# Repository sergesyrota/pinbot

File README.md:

```bash
brew install --HEAD opencv3 --with-contrib
brew install webp

pip install --upgrade pip
pip install virtualenv

echo /usr/local/opt/opencv3/lib/python2.7/site-packages >> /usr/local/lib/python2.7/site-packages/opencv3.pth

# Reload terminal

cd path/to/pinbot

virtualenv -p `which python` .virtualenv
source .virtualenv/bin/activate

pip install -r requirements.txt

```

### Debugging

For debugging place following in the code:

```python
import ipdb; ipdb.set_trace()
```

For debugging serial communication:

```
$ socat -d -d pty,raw,echo=0 pty,raw,echo=0
2016/11/29 08:41:25 socat[43296] N PTY is /dev/ttys003
2016/11/29 08:41:25 socat[43296] N PTY is /dev/ttys004
```
This will create forwarding between 2 serial interfaces. Then you can write into one, and read from another.

Flipper detect frame numbers:

When we want to train flipper on recorded video, we need to know frame numbers that can be considered as "pressing
the button." Both arguments need to be passed (otherwise it doesn't make much sense).

```
--debug-right 244,273,316,349,381,413,445,476,522
--debug-left 594,626,658,691,723,755,787
```

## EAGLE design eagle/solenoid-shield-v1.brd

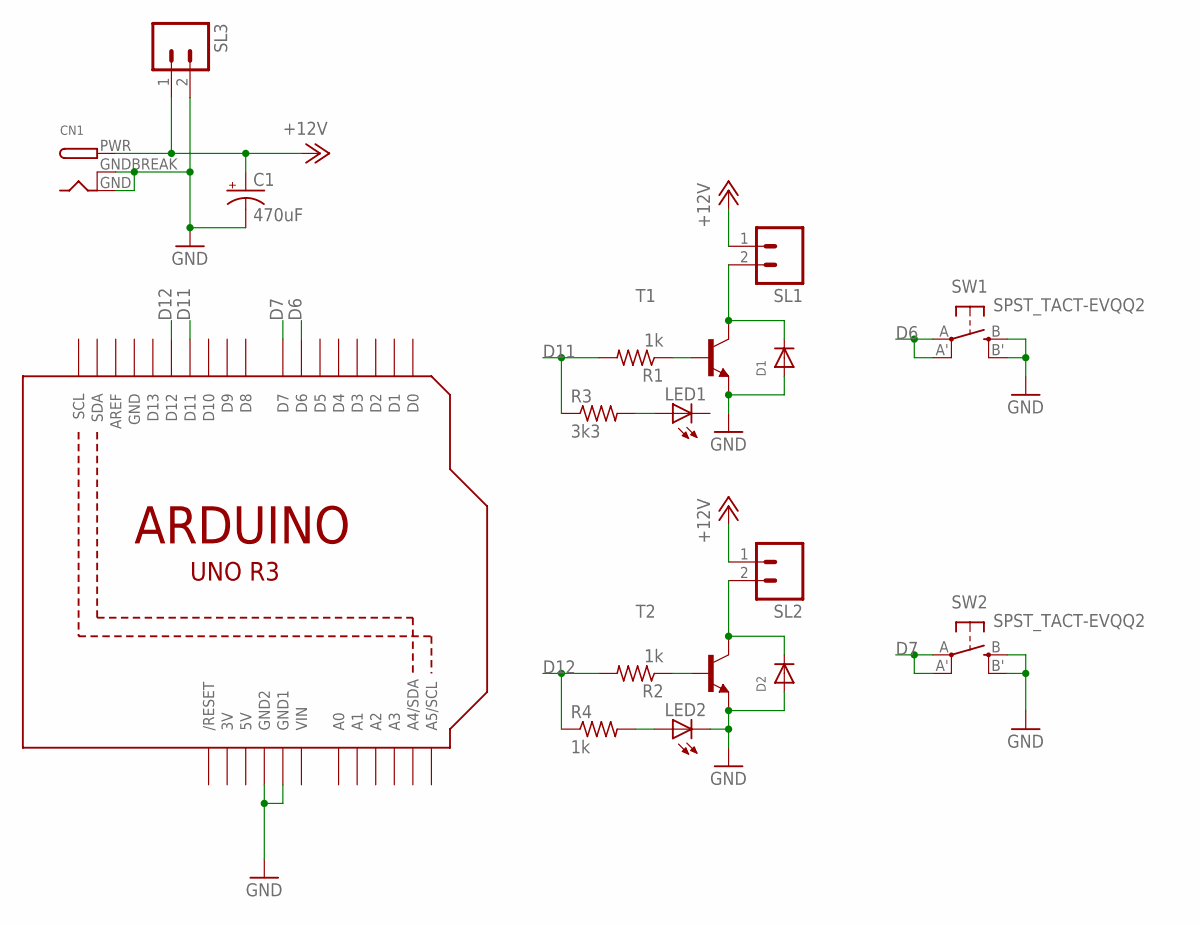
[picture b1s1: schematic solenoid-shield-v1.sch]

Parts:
C1: 470uF; E5-13
CN1: DCBARRELPTH; DCJACK_2MM_PTH
D1, D2: DIODESMA; SMADIODE
LED1, LED2: LEDSMT1206; 1206
Q1: ARDUINOR3-NOIOREF-NOTEXT; ARDUINOR3-NOTEXT-NOIOREF
R1, R2, R4: 1k; R0603
R3: 3k3; R0603
SL1, SL2, SL3: M02; 02P
SW1, SW2: SPST_TACT-EVQQ2; EVQ-Q2
T1, T2: BC808-NPN-SOT23-BEC; SOT23-BEC

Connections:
3V: Q1.3V
5V: Q1.5V
+12V: C1.+, CN1.PWR, SL1.1, SL2.1, SL3.1
D6: Q1.D6, SW1.A, SW1.A' (P1)
D7: Q1.D7, SW2.A, SW2.A' (P1)
D11: Q1.D11, R1.2, R3.1
D12: Q1.D12, R2.2, R4.1
GND: C1.-, CN1.GND, CN1.GNDBREAK, D1.A, D2.A, LED2.C, Q1.GND, Q1.GND1, Q1.GND2, SL3.2, SW1.B (S), SW1.B' (S1), SW2.B (S), SW2.B' (S1), T1.E, T2.E
unnamed: LED2.A, R4.2
unnamed: R1.1, T1.B
unnamed: D1.C, SL1.2, T1.C
unnamed: LED1.A, R3.2
unnamed: D2.C, SL2.2, T2.C
unnamed: R2.1, T2.B
VIN: Q1.VIN

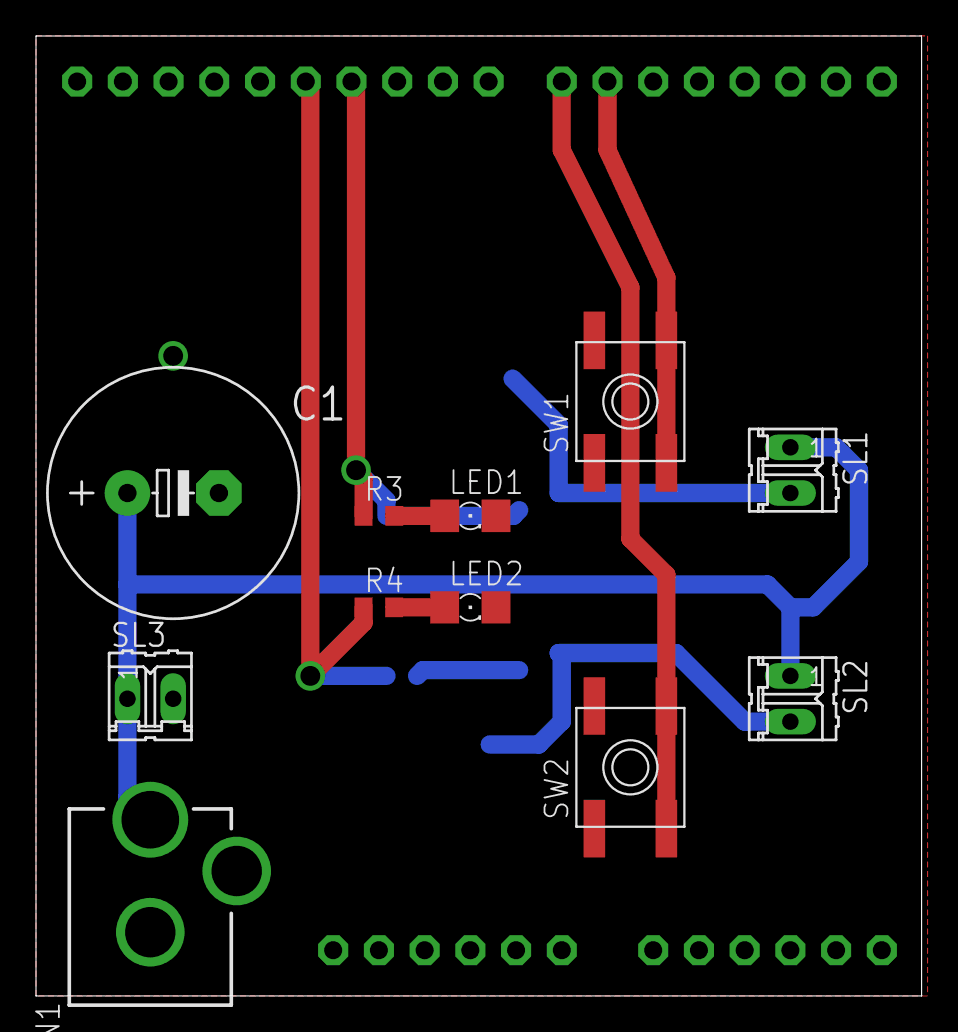
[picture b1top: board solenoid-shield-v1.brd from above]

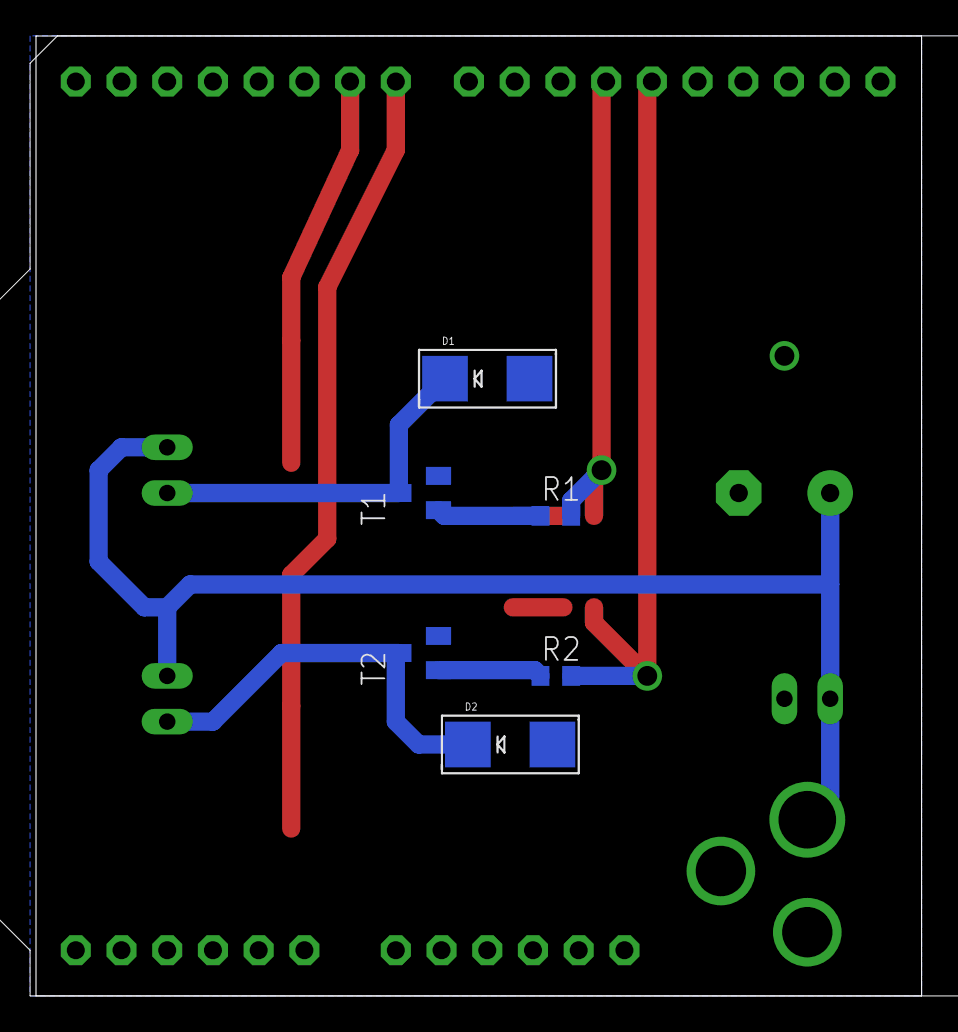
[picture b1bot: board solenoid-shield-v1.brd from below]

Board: 2 copper layers, 49.2 x 53.3 mm, 18 parts (6 on the bottom side), 12 nets.

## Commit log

2016-11-19 Initial prototype of tracker
2016-11-19 Adding gitignore
2016-11-19 Adding basic installation steps
2016-11-19 Fixed readme formatting
2016-11-19 Add tmp and log folders
2016-11-19 Using argparse to specify video source
2016-11-19 Testing multi-ball
2016-11-19 Mention dependencies installation
2016-11-19 Specify OpenCV installation procedure to include all required libraries
2016-11-19 Remove pep8 violations
2016-11-23 Adding 3d model for micro-solenoid model git status
2016-11-23 Removing highlights for some cutouts of the model, so it looks clearer.
2016-11-23 adding some ground work for video-based training.
2016-11-24 Fixed tracking of objects. Added optional output of annotated video for further analysis.
2016-11-24 More refinemenet to the mount, including sliding mount, bug fixes, and actual dimensions of parts.
2016-11-25 Started drawing schematic of arduino shield. Updated gitignore with eagle specific temporary files.
2016-11-25 Added board, and started routing.
2016-11-25 Finished v1 of the shield
2016-11-27 Adding Arduino sketch, first iteration with just buttons, no communication.
2016-11-27 Updating solenoid mounting sketch with multi-magnet support, more square shapes (for easier printing), making things centered (multi-magnet will make things more shifted)
2016-11-27 Started working on communication module. Still work in progress, not tested at all. Updated gitignore for python compiled files too.
2016-11-27 Fix pep8 complaints
2016-11-27 Use new-style class definition
    Detailed description of new-style vs old-style is available in python
    wiki: https://wiki.python.org/moin/NewClassVsClassicClass.
    Please note, that python 3 does not have old-style classes.
2016-11-27 Fix arduino serial communication import
2016-11-27 Make main app script executable
2016-11-27 Add double-dash aliases to script params
2016-11-27 Added extra plastic to decrease solenoid leverage, by eliminating magnet pivot point.
2016-11-28 Fixing misspelled module import, adding serial lib to readme.
2016-11-28 rolling back my 'fix' as I missed commits...
2016-11-29 Replace manual dependencies installation with requirements file
2016-11-29 Add debugging capability description
2016-11-29 Remove single-dashed parameters
2016-11-29 Adding time tracking to live video and output frame.
2016-11-29 Adding serial communication to Arduino. That module is complete now.
2016-11-29 pep8 fixes
2016-11-29 Adding close function, as this seems to be called as destructor.
2016-11-29 Adding state structure to hold current state of different things, and refactored timing to go off of that object too.
2016-11-30 Added some readme on serial debugging witout having Arduino connected. Refactored frame text overlay to be able to add other text, like what commands are firing.
2016-11-30 Fixed serial communication, as self was missing in all write commands
2016-11-30 Adding training skeleton, and a first iteration of training of flipper A.
2016-12-01 Adding argument level support for displaying real time annotated video. Refactoring not to draw on the frame unless we need to show it or record.
2016-12-01 Finished training routine, seems like it. Next step is integration with the flipper interface.
2016-12-01 Adding manual frame-based override for training based on video. Updated readme file with frames we have in current recorded temporary video.
2016-12-02 Added training for flipper B. Updated debug info for a new video that has also ball sequence.
2016-12-02 Basic draft of flipper visual handler
2016-12-02 Finalized flipper implementation
2016-12-02 Add flipper to the main logic
2016-12-02 Added logic for the game itself. Added drawing of learned areas too.
2016-12-03 Updates from the night of hacking.
2016-12-04 Making src compatible with file path or camera number
2016-12-04 Removed sleep in favor of skipping frames when we’re in training mode. Fixed video writer to always get frame size from the stream, instead of having to manually match.
2016-12-04 Removed cooldown multiplier in training, as we’re using background subtractor that’s more dumb, so it will not start ignoring repetitive actions.
2016-12-06 Refactored some code, added 2nd byte to arduino communication protocol to signify delay (in 10ms increments, up to 2550ms).
2016-12-06 Added brute force predictor to tracking. This seems promising, and frame processing time is at a consistent 22ms, so should be good enough (and there is room for improvements!)
2016-12-06 Improved brute force detection, added support for timing error in future prediction, calibrated numbers some more. Still at 22ms processing of each frame, so seems like runctions like area calculatio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
2016-12-10 Major refactoring… Moved to differet background processing for different parts of the game. Changed logic for affected areas to be masks, not rectangles. Added going off of predictors of trajectory, 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
2016-12-16 A few fixes and improvements in the general code, and trying to introduce miltithreading. Right now, seems like the thread does not update class variables accessible by “read” method.
2016-12-17 Finished multithreading implementation, so now camera reads are not blocking processing, and if processing gets slowed down, we will use the latest frame, rather than one with delay.
